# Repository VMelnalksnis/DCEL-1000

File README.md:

# DCEL-1000

DCEL-1000 is a digital DC electronic load.
* Operates between 0 - 500 VDC, 4 μA<sup>1</sup> - 30A (~200 W maximum, depending on cooling solution)
* Two current ranges: 30 A (2 mA<sup>1</sup> resolution) and 50 mA (4 μA<sup>1</sup> resolution)
* Has dedicated voltage sense terminals
* Consists of two parallel MOSFETs with separate current sense and gate drive
* Controlled via opto-isolated 2.5 MHz SPI interface and control signals
* Requires +12 VDC, provides isolated +5 VDC (1 W)

<sup>1</sup> Theoretical resolution without oversampling assuming 2 LSB noise for current sense ADCs, most likely will change

## Table of contents

1. [About the project](#about-the-project)
1. [Project status](#project-status)
1. [Getting started](#getting-started)
	1. [Dependencies](#dependencies)
1. [License](#license)
1. [Authors](#authors)

# About the project

**[Back to top](#table-of-contents)**

# Project status

Currently working on finishing designing the hardware, both electrical and mechanical.

**[Back to top](#table-of-contents)**

# Getting Started

## Dependencies

* [My EAGLE libraries](https://github.com/VMelnalksnis/Eagle-Libraries)

**[Back to top](#table-of-contents)**

# License

Copyright (c) 2018 Valters Melnalksnis

This project is licensed under the MIT License - see [LICENSE.txt](LICENSE.txt) file for details.

**[Back to top](#table-of-contents)**

# Authors

* **[Valters Melnalksnis](https://github.com/vmelnalksnis)** - *Initial work*

**[Back to top](#table-of-contents)**

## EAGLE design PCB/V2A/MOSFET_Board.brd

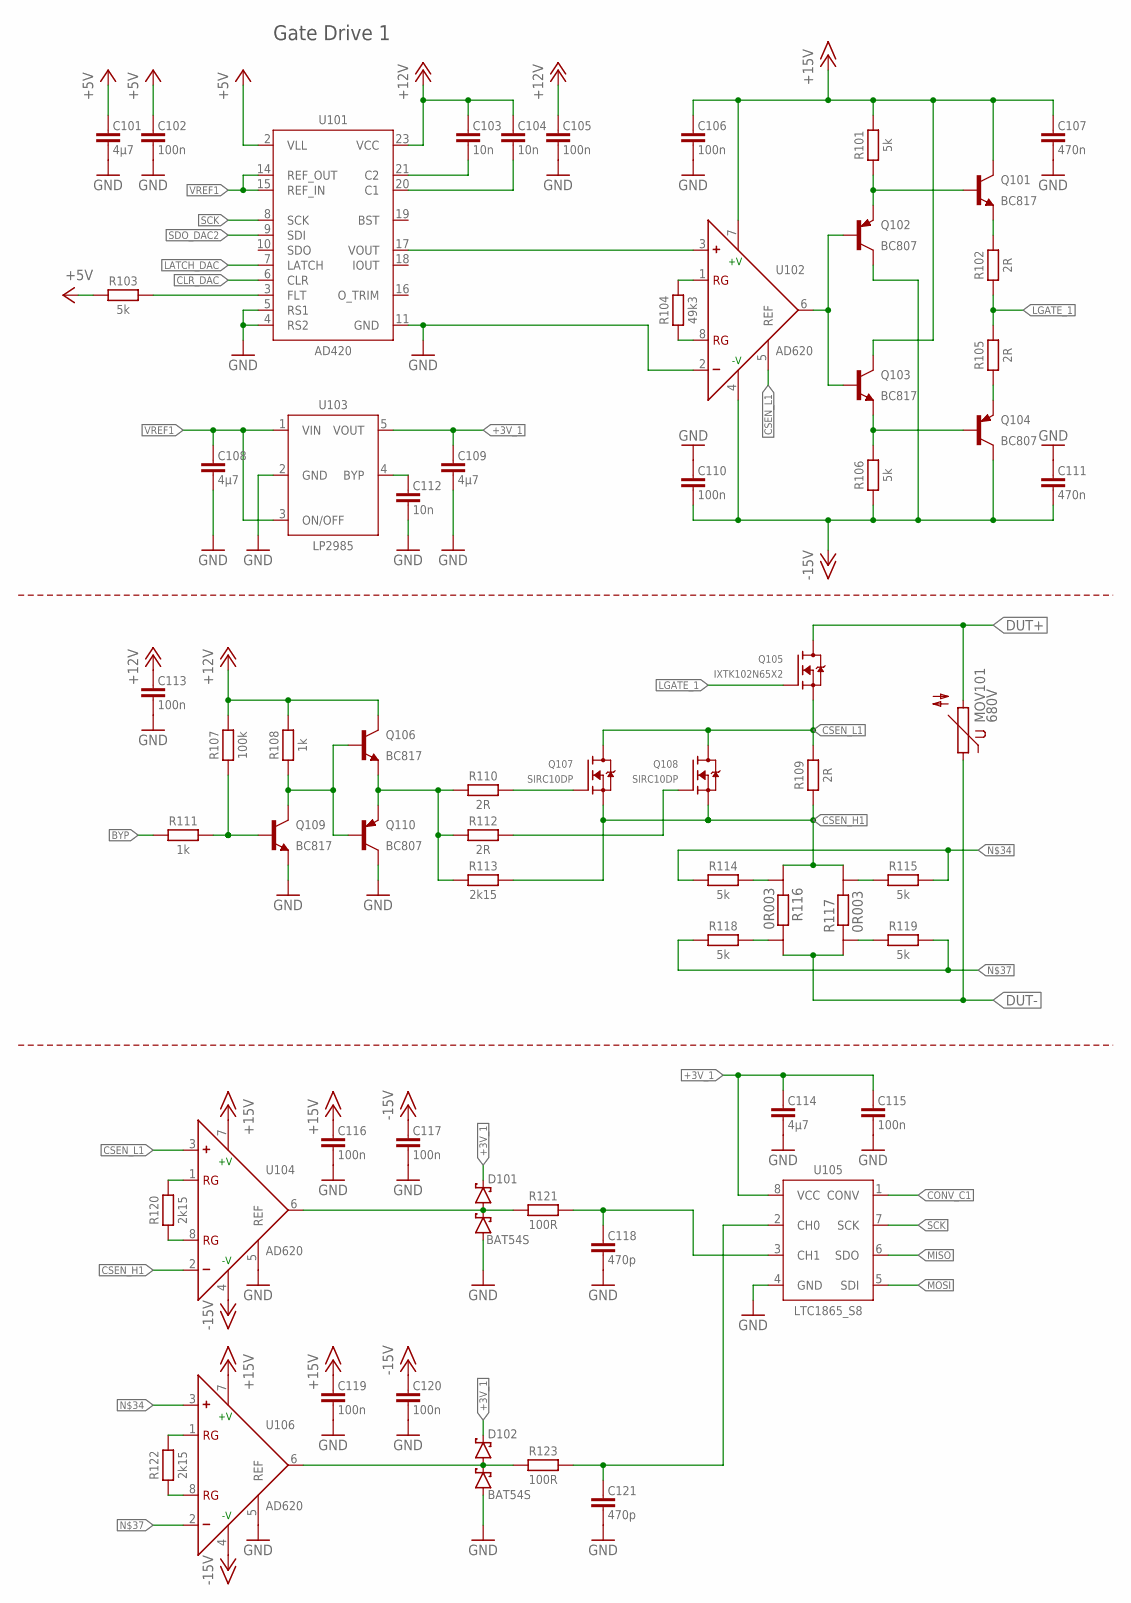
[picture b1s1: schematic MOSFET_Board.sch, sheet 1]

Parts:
C101, C108, C109, C114: 4µ7; CAPC3216X135
C102, C105, C106, C110, C113, C115, C116, C117, C119, C120: 100n; CAPC1508X45
C103, C104, C112: 10n; CAPC1508X45
C107, C111: 470n; CAPC1508X45
C118, C121: 470p; CAPC1508X45
D101, D102: BAT54S; SOT95P230X110-3
MOV101: 680V; S14K680
Q101, Q103, Q106, Q109: BC817; SOT95P240X110-3
Q102, Q104, Q110: BC807; SOT95P240X110-3
Q105: IXTK102N65X2; TO-264P-V
Q107, Q108: SIRC10DP; POWERPAK-SO-8
R101, R103, R106, R114, R115, R118, R119: 5k; RESC1608X70
R102, R105, R109, R110, R112: 2R; RESC3216X71
R104: 49k3; RESC1608X70
R107: 100k; RESC1608X70
R108, R111: 1k; RESC1608X70
R113, R120, R122: 2k15; RESC2012X65
R116, R117: 0R003; WSL3637_0.01
R121, R123: 100R; RESC1608X70
U101: AD420; SOIC127P1032X265-24
U102, U104, U106: AD620; SOIC127P599X175-8
U103: LP2985; SOT95P280X145-5
U105: LTC1865_S8; SOIC127P599X175-8

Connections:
+3V_1: C109.1, C114.1, C115.1, D101.2 (C2), D102.2 (C2), U103.5 (VOUT), U105.8 (VCC); also elsewhere on the board
+5V: C101.1, C102.1, R103.2, U101.2 (VLL); also elsewhere on the board
+12V: C103.1, C104.1, C105.1, C113.1, Q106.3 (C), R107.2, R108.2, U101.23 (VCC); also elsewhere on the board
+15V: C106.1, C107.1, C116.1, C119.1, Q101.3 (C), Q103.3 (C), R101.2, U102.7 (+V), U104.7 (+V), U106.7 (+V); also elsewhere on the board
-15V: C110.2, C111.2, C117.1, C120.1, Q102.3 (C), Q104.3 (C), R106.1, U102.4 (-V), U104.4 (-V), U106.4 (-V); also elsewhere on the board
BPY1G1: Q107.4 (G), R110.2
BYP: R111.1; also elsewhere on the board
BYP1: Q106.2 (E), Q110.2 (E), R110.1, R112.1, R113.1
BYP1G2: Q108.4 (G), R112.2
CLR_DAC: U101.6 (CLR); also elsewhere on the board
CONV_C1: U105.1 (CONV); also elsewhere on the board
CSEN_H1: Q107.1 (S), Q107.2 (S), Q107.3 (S), Q108.1 (S), Q108.2 (S), Q108.3 (S), R109.1, R113.2, R116.I1, R117.I2, U104.2 (-)
CSEN_L1: Q105.3 (S), Q107.5 (D), Q107.6 (D), Q107.7 (D), Q107.8 (D), Q108.5 (D), Q108.6 (D), Q108.7 (D), Q108.8 (D), R109.2, U102.5 (REF), U104.3 (+)
DUT+: MOV101.2, Q105.2 (D); also elsewhere on the board
DUT-: MOV101.1, R116.I2, R117.I1; also elsewhere on the board
GND: C101.2, C102.2, C105.2, C106.2, C107.2, C108.2, C109.2, C110.1, C111.1, C112.2, C113.2, C114.2, C115.2, C116.2, C117.2, C118.2, C119.2, C120.2, C121.2, D101.1 (A1), D102.1 (A1), Q109.2 (E), Q110.3 (C), U101.4 (RS2), U101.5 (RS1), U101.11 (GND), U102.2 (-), U103.2 (GND), U104.5 (REF), U105.4 (GND), U106.5 (REF); also elsewhere on the board
HIGHC1: C121.1, R123.2, U105.2 (CH0)
LATCH_DAC: U101.7 (LATCH); also elsewhere on the board
LGATE_1: Q105.1 (G), R102.1, R105.2
LOWC1: C118.1, R121.2, U105.3 (CH1)
MISO: U105.6 (SDO); also elsewhere on the board
MOSI: U105.5 (SDI); also elsewhere on the board
unnamed: Q101.1 (B), Q102.2 (E), R101.1
unnamed: R104.2, U102.1 (RG)
unnamed: C103.2, U101.21 (C2)
unnamed: C104.2, U101.20 (C1)
unnamed: Q106.1 (B), Q109.3 (C), Q110.1 (B), R108.1
unnamed: R104.1, U102.8 (RG)
unnamed: D102.3 (C1A2), R123.1, U106.6 (OUT)
unnamed: Q109.1 (B), R107.1, R111.2
unnamed: U101.17 (VOUT), U102.3 (+)
unnamed: C112.1, U103.4 (BYP)
unnamed: Q104.2 (E), R105.1
unnamed: Q101.2 (E), R102.2
unnamed: D101.3 (C1A2), R121.1, U104.6 (OUT)
unnamed: R115.2, R117.E2
unnamed: R114.1, R115.1, U106.3 (+)
unnamed: R116.E2, R118.1
unnamed: R118.2, R119.2, U106.2 (-)
unnamed: R117.E1, R119.1
unnamed: R114.2, R116.E1
unnamed: R103.1, U101.3 (FLT)
unnamed: Q102.1 (B), Q103.1 (B), U102.6 (OUT)
unnamed: Q103.2 (E), Q104.1 (B), R106.2
RG1_L3: R122.2, U106.1 (RG)
RG1_L4: R120.2, U104.1 (RG)
RG2_L3: R122.1, U106.8 (RG)
RG2_L4: R120.1, U104.8 (RG)
SCK: U101.8 (SCK), U105.7 (SCK); also elsewhere on the board
SDO_DAC2: U101.9 (SDI); also elsewhere on the board
VREF1: C108.1, U101.14 (REF_OUT), U101.15 (REF_IN), U103.1 (VIN), U103.3 (ON/OFF)

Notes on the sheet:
Gate Drive 1

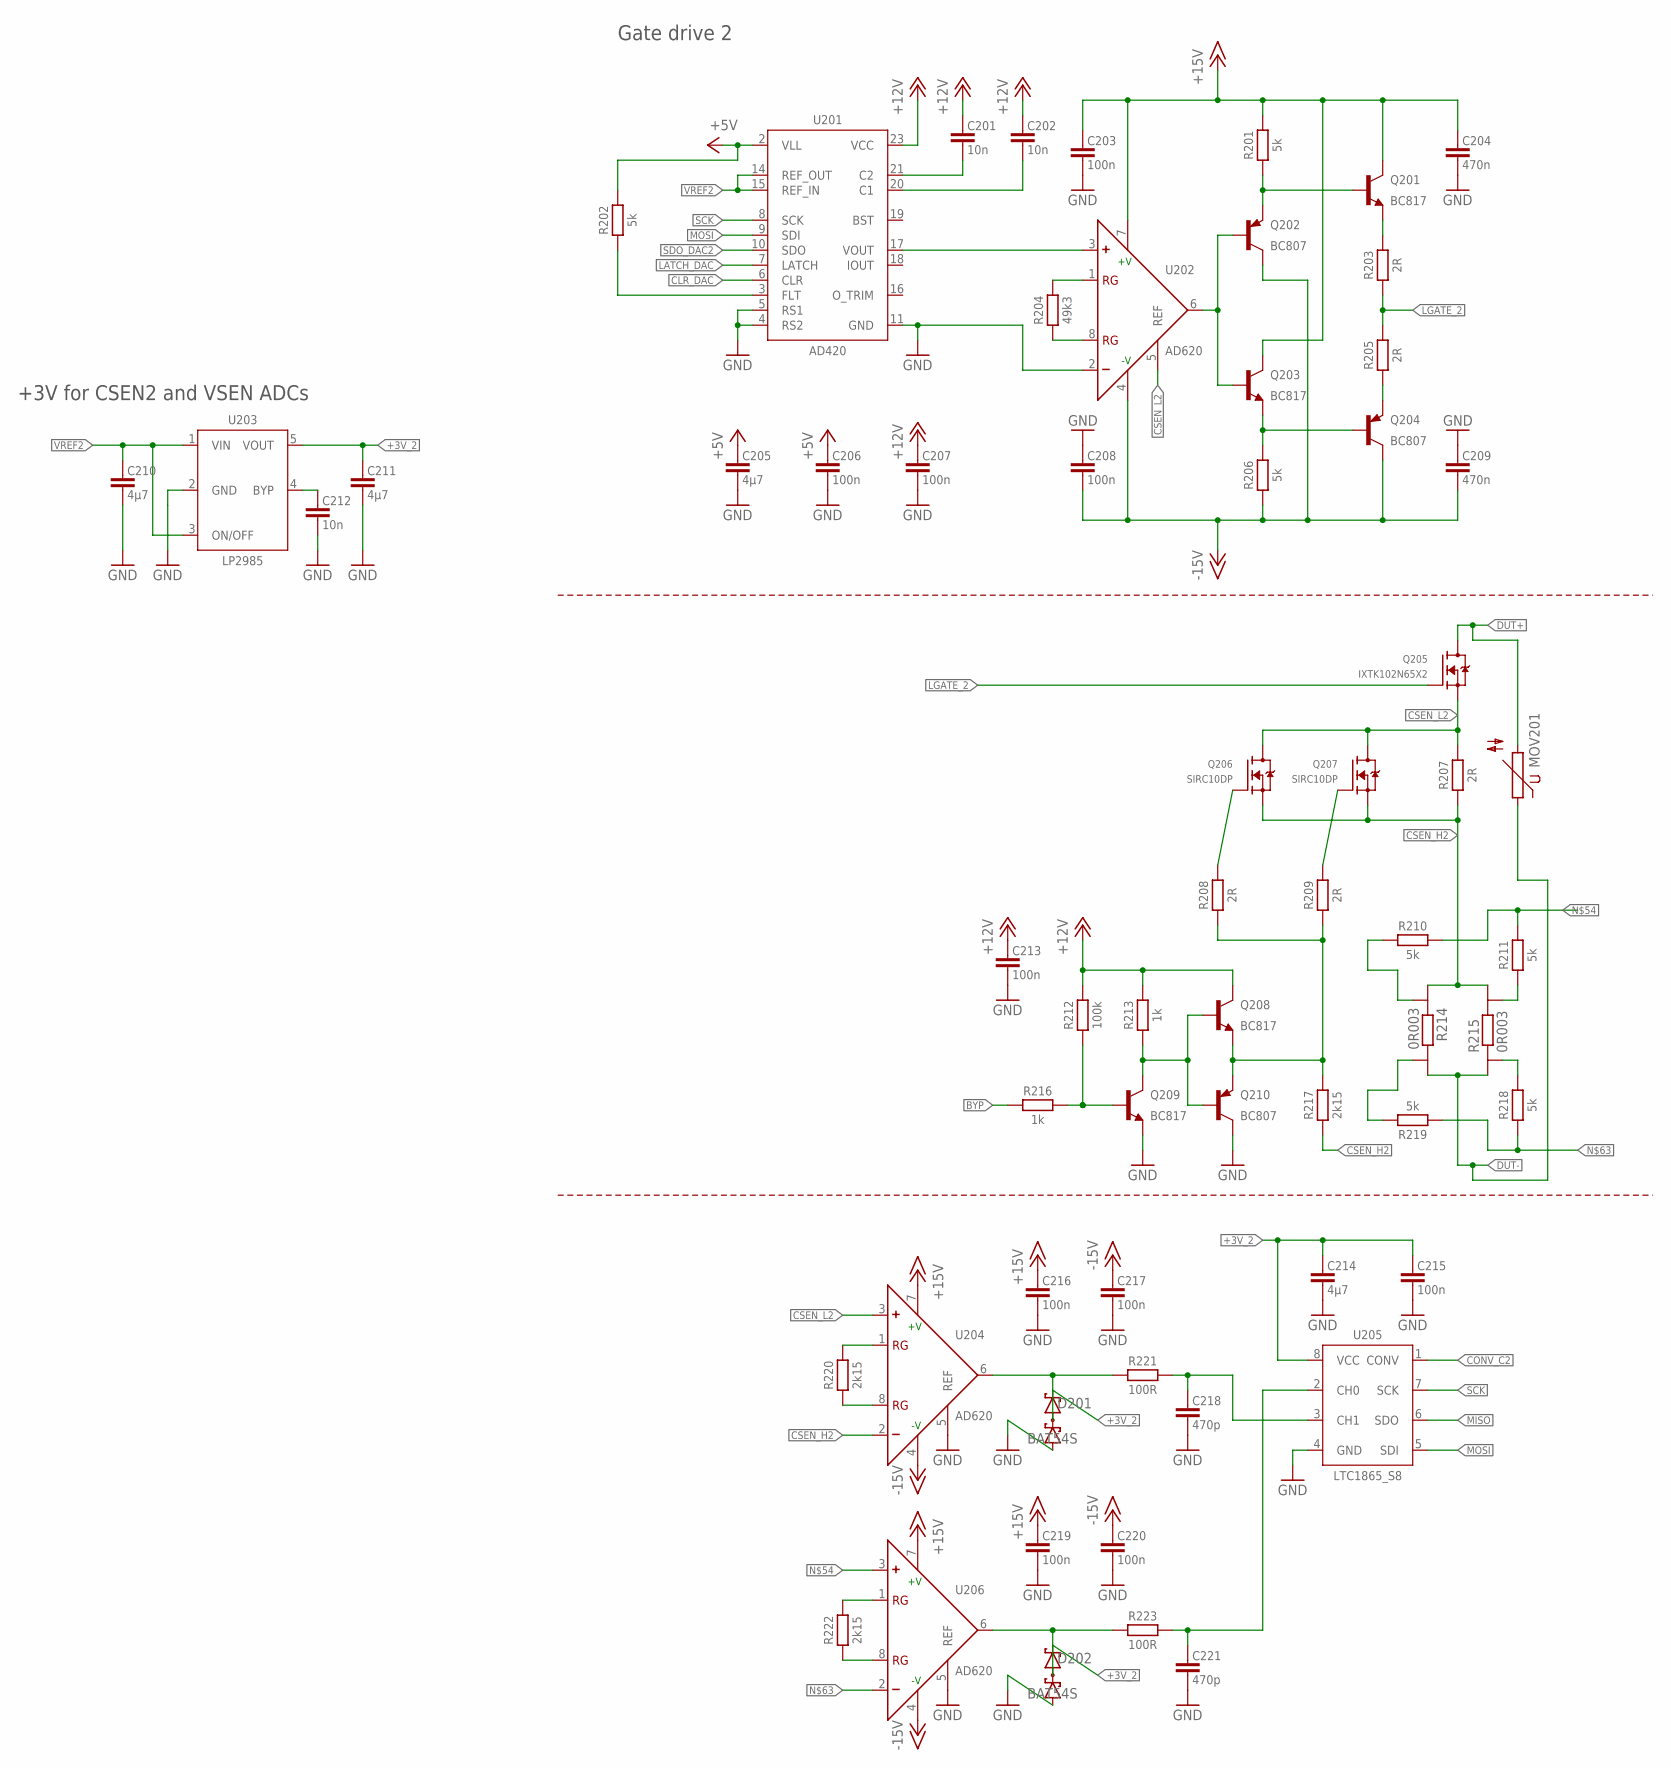
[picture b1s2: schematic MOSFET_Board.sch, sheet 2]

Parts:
C201, C202, C212: 10n; CAPC1508X45
C203, C206, C207, C208, C213, C215, C216, C217, C219, C220: 100n; CAPC1508X45
C204, C209: 470n; CAPC1508X45
C205, C210, C211, C214: 4µ7; CAPC3216X135
C218, C221: 470p; CAPC1508X45
D201, D202: BAT54S; SOT95P230X110-3
MOV201: MOV-14X7.4; S14K680
Q201, Q203, Q208, Q209: BC817; SOT95P240X110-3
Q202, Q204, Q210: BC807; SOT95P240X110-3
Q205: IXTK102N65X2; TO-264P-V
Q206, Q207: SIRC10DP; POWERPAK-SO-8
R201, R202, R206, R210, R211, R218, R219: 5k; RESC1608X70
R203, R205, R207, R208, R209: 2R; RESC3216X71
R204: 49k3; RESC1608X70
R212: 100k; RESC1608X70
R213, R216: 1k; RESC1608X70
R214, R215: 0R003; WSL3637_0.01
R217, R220, R222: 2k15; RESC2012X65
R221, R223: 100R; RESC1608X70
U201: AD420; SOIC127P1032X265-24
U202, U204, U206: AD620; SOIC127P599X175-8
U203: LP2985; SOT95P280X145-5
U205: LTC1865_S8; SOIC127P599X175-8

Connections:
+3V_2: C211.1, C214.1, C215.1, D201.2 (C2), D202.2 (C2), U203.5 (VOUT), U205.8 (VCC)
+5V: C205.1, C206.1, R202.2, U201.2 (VLL); also elsewhere on the board
+12V: C201.1, C202.1, C207.1, C213.1, Q208.3 (C), R212.2, R213.2, U201.23 (VCC); also elsewhere on the board
+15V: C203.1, C204.1, C216.1, C219.1, Q201.3 (C), Q203.3 (C), R201.2, U202.7 (+V), U204.7 (+V), U206.7 (+V); also elsewhere on the board
-15V: C208.2, C209.2, C217.1, C220.1, Q202.3 (C), Q204.3 (C), R206.1, U202.4 (-V), U204.4 (-V), U206.4 (-V); also elsewhere on the board
BYP: R216.1; also elsewhere on the board
BYP2: Q208.2 (E), Q210.2 (E), R208.1, R209.1, R217.2
BYP2G1: Q206.4 (G), R208.2
BYP2G2: Q207.4 (G), R209.2
CLR_DAC: U201.6 (CLR); also elsewhere on the board
CONV_C2: U205.1 (CONV); also elsewhere on the board
CSEN_H2: Q206.1 (S), Q206.2 (S), Q206.3 (S), Q207.1 (S), Q207.2 (S), Q207.3 (S), R207.1, R214.I1, R215.I2, R217.1, U204.2 (-)
CSEN_L2: Q205.3 (S), Q206.5 (D), Q206.6 (D), Q206.7 (D), Q206.8 (D), Q207.5 (D), Q207.6 (D), Q207.7 (D), Q207.8 (D), R207.2, U202.5 (REF), U204.3 (+)
DUT+: MOV201.2, Q205.2 (D); also elsewhere on the board
DUT-: MOV201.1, R214.I2, R215.I1; also elsewhere on the board
GND: C203.2, C204.2, C205.2, C206.2, C207.2, C208.1, C209.1, C210.2, C211.2, C212.2, C213.2, C214.2, C215.2, C216.2, C217.2, C218.2, C219.2, C220.2, C221.2, D201.1 (A1), D202.1 (A1), Q209.2 (E), Q210.3 (C), U201.4 (RS2), U201.5 (RS1), U201.11 (GND), U202.2 (-), U203.2 (GND), U204.5 (REF), U205.4 (GND), U206.5 (REF); also elsewhere on the board
HIGHC2: C221.1, R223.2, U205.2 (CH0)
LATCH_DAC: U201.7 (LATCH); also elsewhere on the board
LGATE_2: Q205.1 (G), R203.1, R205.2
LOWC2: C218.1, R221.2, U205.3 (CH1)
MISO: U205.6 (SDO); also elsewhere on the board
MOSI: U201.9 (SDI), U205.5 (SDI); also elsewhere on the board
unnamed: Q201.1 (B), Q202.2 (E), R201.1
unnamed: Q204.2 (E), R205.1
unnamed: Q201.2 (E), R203.2
unnamed: Q208.1 (B), Q209.3 (C), Q210.1 (B), R213.1
unnamed: Q209.1 (B), R212.1, R216.2
unnamed: R210.1, R214.E1
unnamed: C201.2, U201.21 (C2)
unnamed: C202.2, U201.20 (C1)
unnamed: Q202.1 (B), Q203.1 (B), U202.6 (OUT)
unnamed: Q203.2 (E), Q204.1 (B), R206.2
unnamed: R202.1, U201.3 (FLT)
unnamed: R211.1, R215.E2
unnamed: R204.2, U202.1 (RG)
unnamed: R204.1, U202.8 (RG)
unnamed: U201.17 (VOUT), U202.3 (+)
unnamed: R215.E1, R218.2
unnamed: R214.E2, R219.2
unnamed: R210.2, R211.2, U206.3 (+)
unnamed: D202.3 (C1A2), R223.1, U206.6 (OUT)
unnamed: D201.3 (C1A2), R221.1, U204.6 (OUT)
unnamed: C212.1, U203.4 (BYP)
unnamed: R218.1, R219.1, U206.2 (-)
RG1_L1: R222.2, U206.1 (RG)
RG1_L2: R220.2, U204.1 (RG)
RG2_L1: R222.1, U206.8 (RG)
RG2_L2: R220.1, U204.8 (RG)
SCK: U201.8 (SCK), U205.7 (SCK); also elsewhere on the board
SDO_DAC2: U201.10 (SDO); also elsewhere on the board
VREF2: C210.1, U201.14 (REF_OUT), U201.15 (REF_IN), U203.1 (VIN), U203.3 (ON/OFF)

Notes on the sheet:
Gate drive 2
+3V for CSEN2 and VSEN ADCs

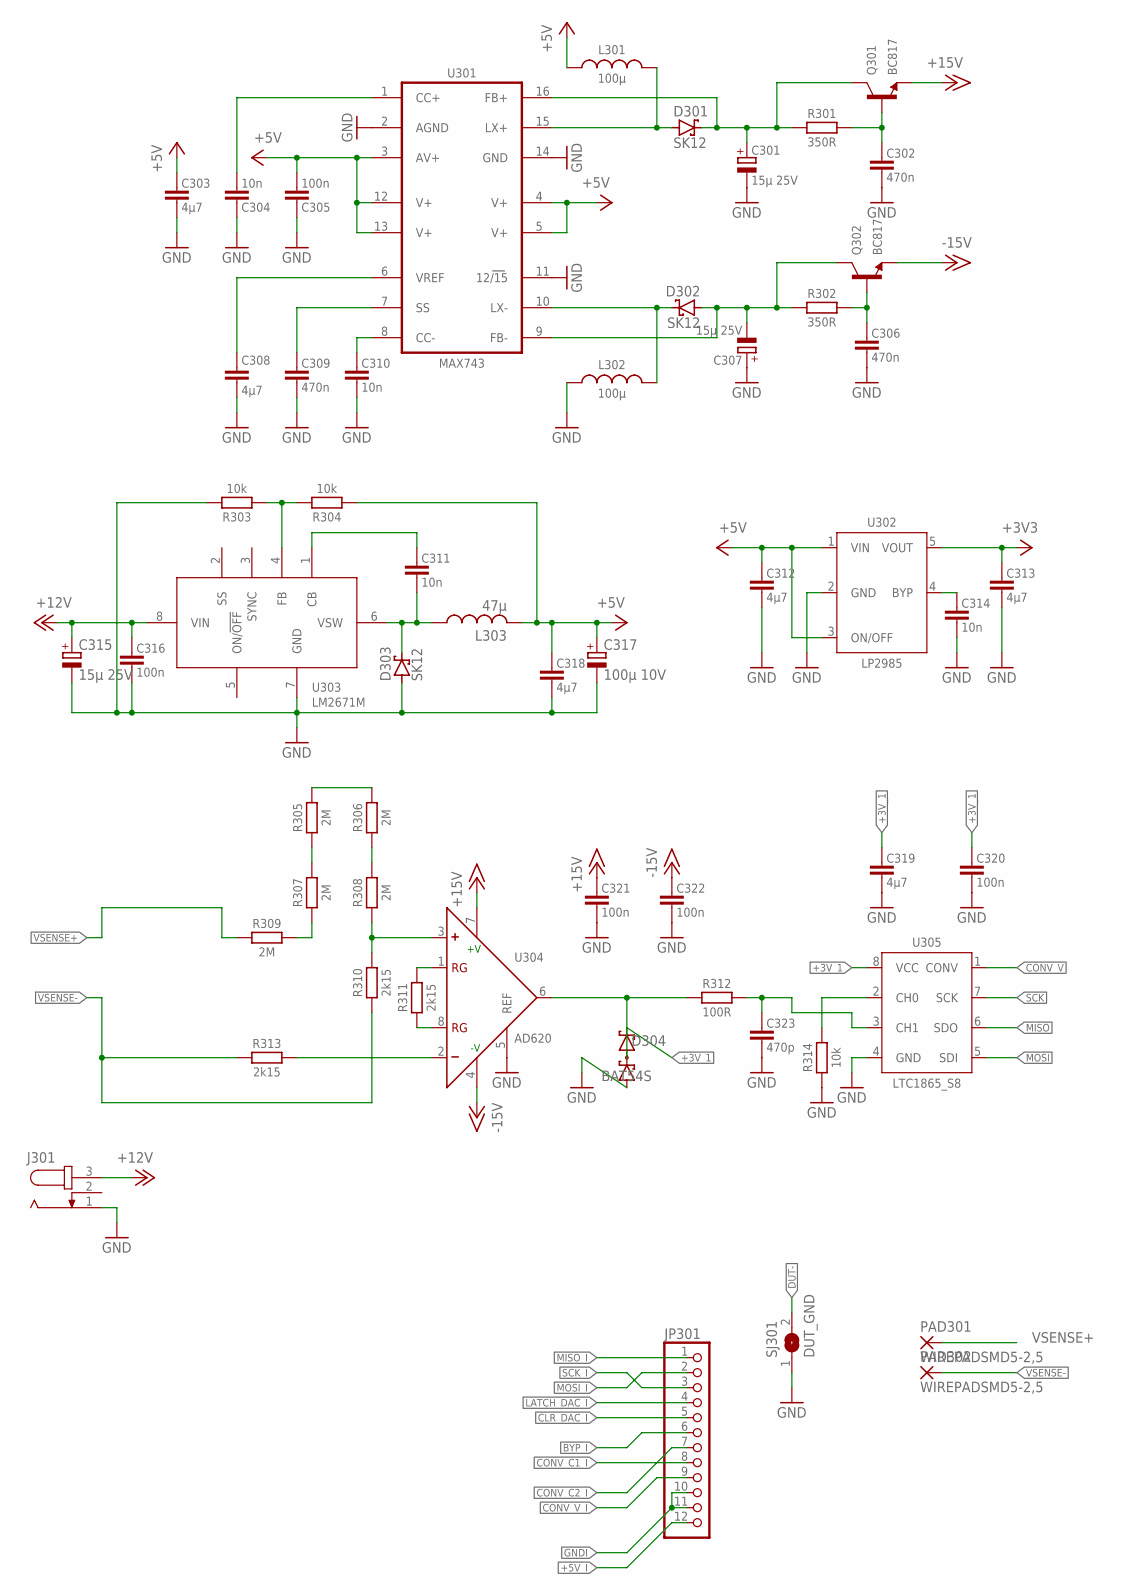
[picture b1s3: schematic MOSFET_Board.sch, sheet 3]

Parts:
C301, C307, C315: 15µ 25V; CAPCP7343X310
C302, C306, C309: 470n; CAPC1508X45
C303, C308, C312, C313, C318, C319: 4µ7; CAPC3216X135
C304, C310, C311, C314: 10n; CAPC1508X45
C305, C316, C320, C321, C322: 100n; CAPC1508X45
C317: 100µ 10V; CAPCP7343X310
C323: 470p; CAPC1508X45
D301, D302, D303: SK12; DIOM4336X262
D304: BAT54S; SOT95P230X110-3
J301: JACK-PLUG-2.5; SPC4078
JP301: PINHD-1X12; 1X12
L301, L302: 100µ; SRN5040
L303: 47µ; SRN5040
PAD301, PAD302: WIREPADSMD5-2,5; 5-2,5
Q301, Q302: BC817; SOT95P240X110-3
R301, R302: 350R; RESC1608X70
R303, R304, R314: 10k; RESC1608X70
R305, R306, R307, R308, R309: 2M; RESC3216X71
R310, R311, R313: 2k15; RESC2012X65
R312: 100R; RESC1608X70
SJ301: DUT_GND; SJW
U301: MAX743; SOIC127P1032X265-16
U302: LP2985; SOT95P280X145-5
U303: LM2671M; SOIC127P599X175-8
U304: AD620; SOIC127P599X175-8
U305: LTC1865_S8; SOIC127P599X175-8

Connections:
+3V3: C313.1, U302.5 (VOUT); also elsewhere on the board
+3V_1: C319.1, C320.1, D304.2 (C2), U305.8 (VCC); also elsewhere on the board
+5V: C303.1, C305.2, C312.1, C317.1 (+), C318.1, L301.1, L303.2, R304.1, U301.3 (AV+), U301.4 (V+), U301.5 (V+), U301.12 (V+), U301.13 (V+), U302.1 (VIN), U302.3 (ON/OFF); also elsewhere on the board
+5V_I: JP301.12; also elsewhere on the board
+12V: C315.1 (+), C316.1, J301.3, U303.8 (VIN); also elsewhere on the board
+15V: C321.1, Q301.2 (E), U304.7 (+V); also elsewhere on the board
-15V: C322.1, Q302.2 (E), U304.4 (-V); also elsewhere on the board
BYP_I: JP301.6; also elsewhere on the board
CLR_DAC_I: JP301.5; also elsewhere on the board
CONV_C1_I: JP301.8; also elsewhere on the board
CONV_C2_I: JP301.7; also elsewhere on the board
CONV_V: U305.1 (CONV); also elsewhere on the board
CONV_V_I: JP301.9; also elsewhere on the board
DUT-: SJ301.2; also elsewhere on the board
GND: C301.2 (-), C302.2, C303.2, C304.1, C305.1, C306.2, C307.1 (+), C308.2, C309.2, C310.2, C312.2, C313.2, C314.2, C315.2 (-), C316.2, C317.2 (-), C318.2, C319.2, C320.2, C321.2, C322.2, C323.2, D303.2 (A), D304.1 (A1), J301.1, L302.2, R303.2, R314.1, SJ301.1, U301.2 (AGND), U301.11 (12/15), U301.14 (GND), U302.2 (GND), U303.7 (GND), U304.5 (REF), U305.4 (GND); also elsewhere on the board
GNDI: JP301.10, JP301.11; also elsewhere on the board
LATCH_DAC_I: JP301.4; also elsewhere on the board
MISO: U305.6 (SDO); also elsewhere on the board
MISO_I: JP301.1; also elsewhere on the board
MOSI: U305.5 (SDI); also elsewhere on the board
MOSI_I: JP301.2; also elsewhere on the board
unnamed: C311.1, U303.1 (CB)
unnamed: C311.2, D303.1 (C), L303.1, U303.6 (VSW)
unnamed: R303.1, R304.2, U303.4 (FB)
unnamed: D304.3 (C1A2), R312.1, U304.6 (OUT)
unnamed: R306.1, R308.2
unnamed: R305.2, R306.2
unnamed: R305.1, R307.2
unnamed: R314.2, U305.2 (CH0)
unnamed: R308.1, R310.2, U304.3 (+)
unnamed: C323.1, R312.2, U305.3 (CH1)
unnamed: R307.1, R309.2
unnamed: R313.2, U304.2 (-)
unnamed: C310.1, U301.8 (CC-)
unnamed: C309.1, U301.7 (SS)
unnamed: C304.2, U301.1 (CC+)
unnamed: D301.2 (A), L301.2, U301.15 (LX+)
unnamed: C314.1, U302.4 (BYP)
unnamed: D302.1 (C), L302.1, U301.10 (LX-)
unnamed: C301.1 (+), D301.1 (C), Q301.3 (C), R301.1, U301.16 (FB+)
unnamed: C302.1, Q301.1 (B), R301.2
unnamed: C307.2 (-), D302.2 (A), Q302.3 (C), R302.1, U301.9 (FB-)
unnamed: C306.1, Q302.1 (B), R302.2
RG1_H6: R311.2, U304.1 (RG)
RG2_H6: R311.1, U304.8 (RG)
SCK: U305.7 (SCK); also elsewhere on the board
SCK_I: JP301.3; also elsewhere on the board
VREF_MAX743: C308.1, U301.6 (VREF)
VSENSE+: PAD301.1, R309.1
VSENSE-: PAD302.1, R310.1, R313.1

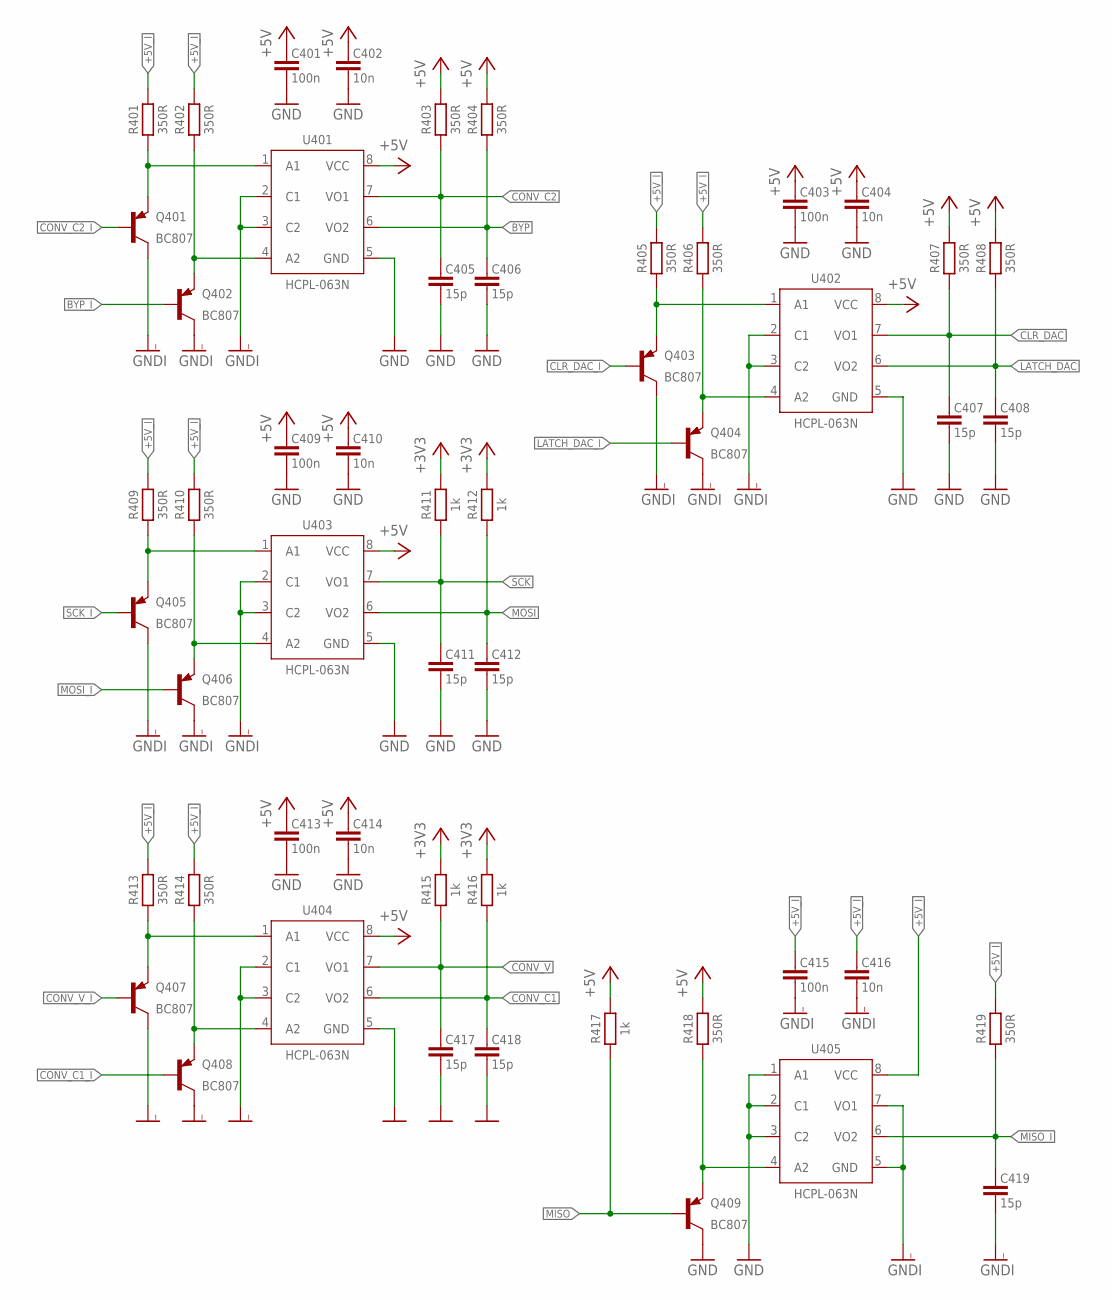
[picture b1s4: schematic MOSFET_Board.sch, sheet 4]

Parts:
C401, C403, C409, C413, C415: 100n; CAPC1508X45
C402, C404, C410, C414, C416: 10n; CAPC1508X45
C405, C406, C407, C408, C411, C412, C417, C418, C419: 15p; CAPC1508X45
Q401, Q402, Q403, Q404, Q405, Q406, Q407, Q408, Q409: BC807; SOT95P240X110-3
R401, R402, R403, R404, R405, R406, R407, R408, R409, R410, R413, R414, R418, R419: 350R; RESC1608X70
R411, R412, R415, R416, R417: 1k; RESC1608X70
U401, U402, U403, U404, U405: HCPL-063N; SOIC127P599X175-8

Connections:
+3V3: R411.2, R412.2, R415.2, R416.2; also elsewhere on the board
+5V: C401.1, C402.1, C403.1, C404.1, C409.1, C410.1, C413.1, C414.1, R403.2, R404.2, R407.2, R408.2, R417.2, R418.2, U401.8 (VCC), U402.8 (VCC), U403.8 (VCC), U404.8 (VCC); also elsewhere on the board
+5V_I: C415.1, C416.1, R401.2, R402.2, R405.2, R406.2, R409.2, R410.2, R413.2, R414.2, R419.2, U405.8 (VCC); also elsewhere on the board
BYP: C406.1, R404.1, U401.6 (VO2); also elsewhere on the board
BYP_I: Q402.1 (B); also elsewhere on the board
CLR_DAC: C407.1, R407.1, U402.7 (VO1); also elsewhere on the board
CLR_DAC_I: Q403.1 (B); also elsewhere on the board
CONV_C1: C418.1, R416.1, U404.6 (VO2); also elsewhere on the board
CONV_C1_I: Q408.1 (B); also elsewhere on the board
CONV_C2: C405.1, R403.1, U401.7 (VO1); also elsewhere on the board
CONV_C2_I: Q401.1 (B); also elsewhere on the board
CONV_V: C417.1, R415.1, U404.7 (VO1); also elsewhere on the board
CONV_V_I: Q407.1 (B); also elsewhere on the board
GND: C401.2, C402.2, C403.2, C404.2, C405.2, C406.2, C407.2, C408.2, C409.2, C410.2, C411.2, C412.2, C413.2, C414.2, C417.2, C418.2, Q409.3 (C), U401.5 (GND), U402.5 (GND), U403.5 (GND), U404.5 (GND), U405.1 (A1), U405.2 (C1), U405.3 (C2); also elsewhere on the board
GNDI: C415.2, C416.2, C419.2, Q401.3 (C), Q402.3 (C), Q403.3 (C), Q404.3 (C), Q405.3 (C), Q406.3 (C), Q407.3 (C), Q408.3 (C), U401.2 (C1), U401.3 (C2), U402.2 (C1), U402.3 (C2), U403.2 (C1), U403.3 (C2), U404.2 (C1), U404.3 (C2), U405.5 (GND), U405.7 (VO1); also elsewhere on the board
LATCH_DAC: C408.1, R408.1, U402.6 (VO2); also elsewhere on the board
LATCH_DAC_I: Q404.1 (B); also elsewhere on the board
MISO: Q409.1 (B), R417.1; also elsewhere on the board
MISO_I: C419.1, R419.1, U405.6 (VO2); also elsewhere on the board
MOSI: C412.1, R412.1, U403.6 (VO2); also elsewhere on the board
MOSI_I: Q406.1 (B); also elsewhere on the board
unnamed: Q409.2 (E), R418.1, U405.4 (A2)
unnamed: Q405.2 (E), R409.1, U403.1 (A1)
unnamed: Q406.2 (E), R410.1, U403.4 (A2)
unnamed: Q401.2 (E), R401.1, U401.1 (A1)
unnamed: Q402.2 (E), R402.1, U401.4 (A2)
unnamed: Q403.2 (E), R405.1, U402.1 (A1)
unnamed: Q404.2 (E), R406.1, U402.4 (A2)
unnamed: Q407.2 (E), R413.1, U404.1 (A1)
unnamed: Q408.2 (E), R414.1, U404.4 (A2)
SCK: C411.1, R411.1, U403.7 (VO1); also elsewhere on the board
SCK_I: Q405.1 (B); also elsewhere on the board

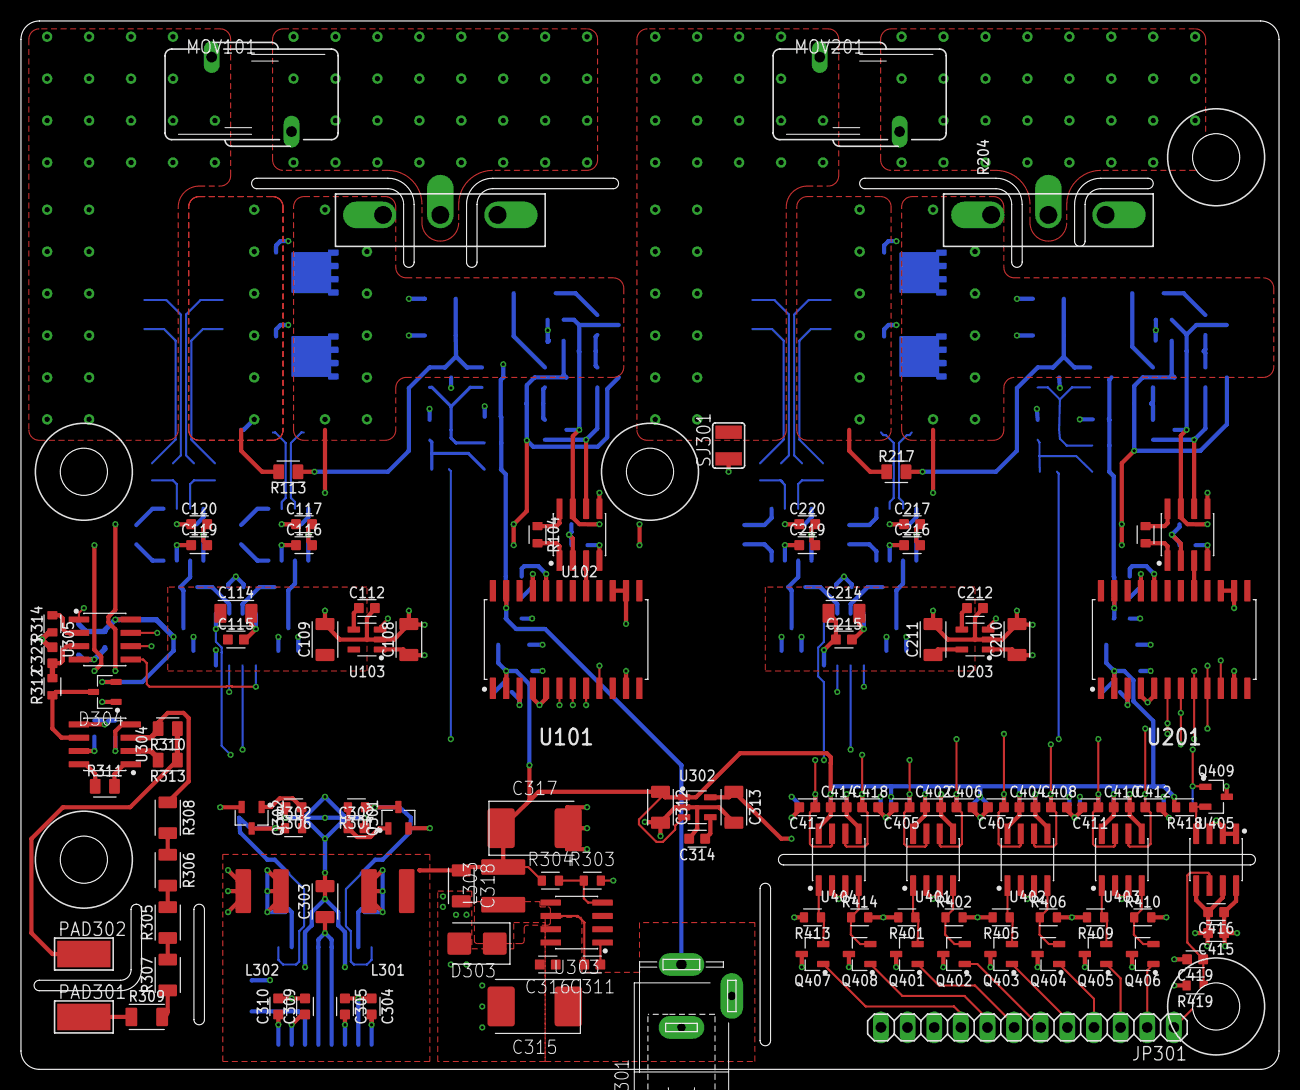
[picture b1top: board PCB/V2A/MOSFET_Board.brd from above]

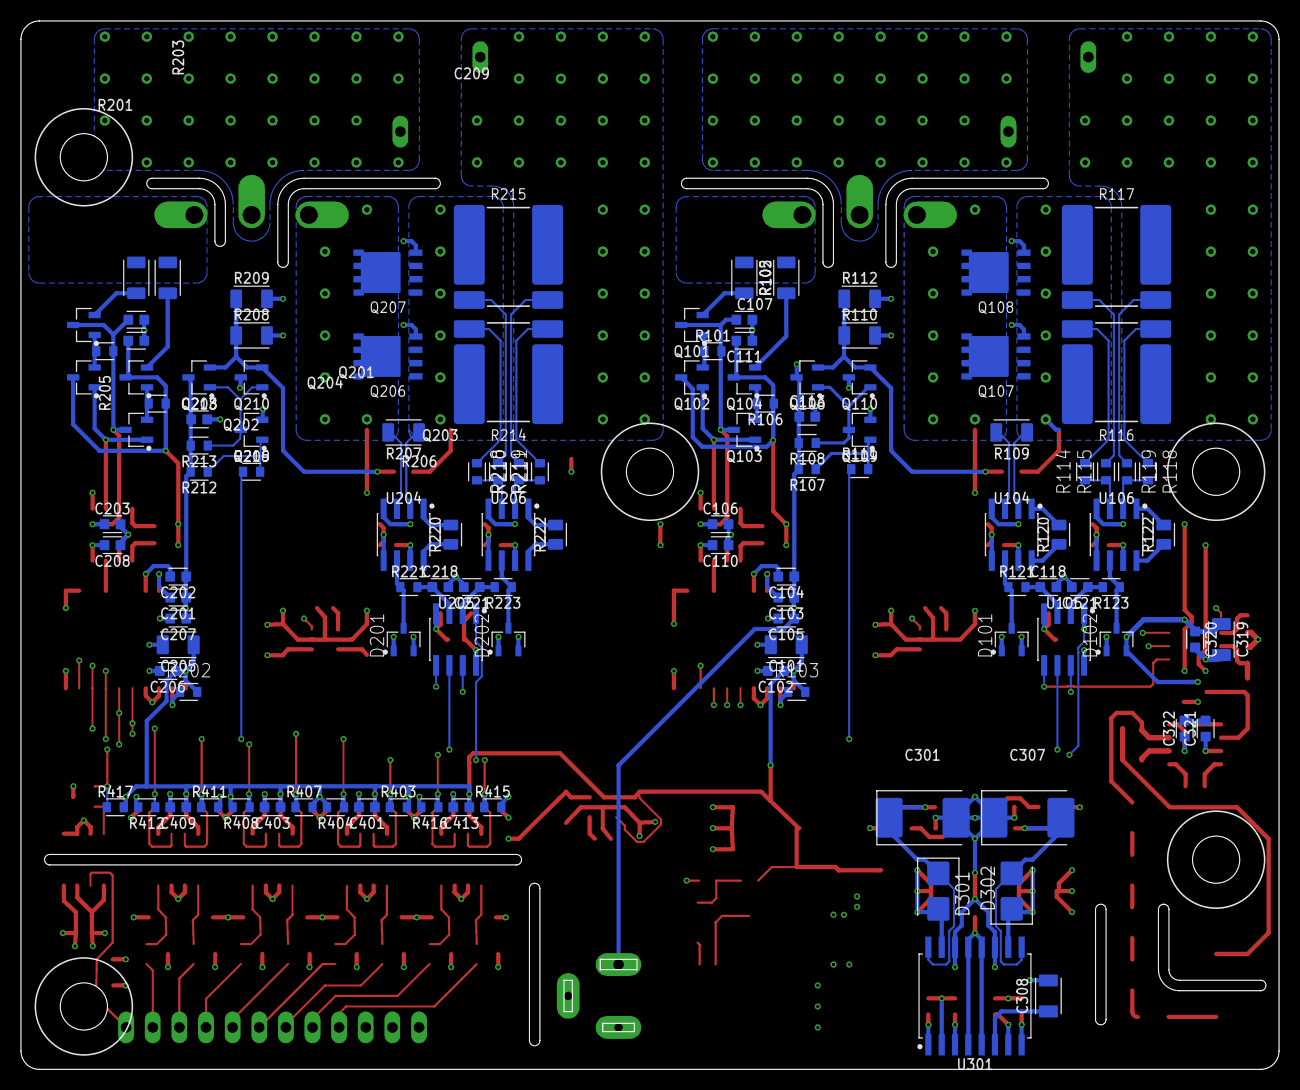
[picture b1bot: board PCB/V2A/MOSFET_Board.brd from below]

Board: 4 copper layers, 120.0 x 100.0 mm, 239 parts (117 on the bottom side), 137 nets.

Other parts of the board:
U$1, U$2, U$3, U$4, U$5: M4
